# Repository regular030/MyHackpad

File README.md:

# BOM | SaturnBoard

- 16x 1N4148 Diodes
- 1x OLED 128x32 (Adafruit_SSD1306 would be good but not needed) 
- 16x Push Switches (SW_Push)
- 16x White keycaps
- 1x Seeed XIAO RP2040 MCU

THE REPO HAS BEEN CHANGED TO https://github.com/regular030/hackpad/tree/main

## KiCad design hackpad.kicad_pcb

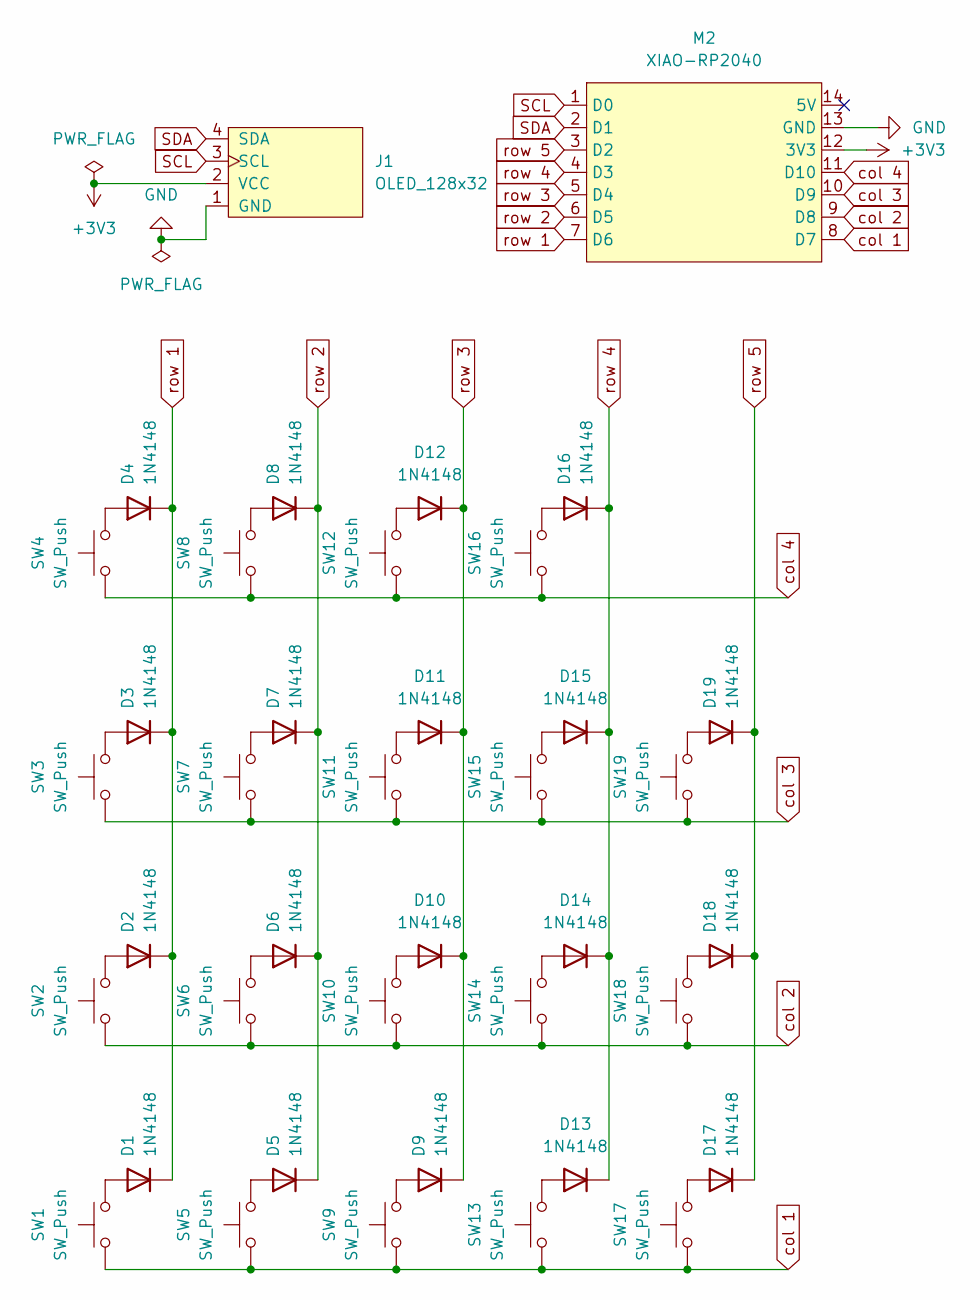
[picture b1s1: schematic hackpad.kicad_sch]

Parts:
D1, D2, D3, D4, D5, D6, D7, D8, D9, D10, D11, D12, D13, D14, D15, D16, D17, D18, D19: 1N4148; D_DO-35_SOD27_P7.62mm_Horizontal
J1: OLED_128x32; SSD1306-0.91-OLED-4pin-128x32
M2: XIAO-RP2040
SW1, SW2, SW3, SW4, SW5, SW6, SW7, SW8, SW9, SW10, SW11, SW12, SW13, SW14, SW15, SW16, SW17, SW18, SW19: SW_Push; SW_Cherry_MX_1.00u_PCB

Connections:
+3V3: J1.2 (VCC), M2.12 (3V3)
GND: J1.1 (GND), M2.13 (GND)
unnamed: D1.2 (A), SW1.2
unnamed: D2.2 (A), SW2.2
unnamed: D3.2 (A), SW3.2
unnamed: D4.2 (A), SW4.2
unnamed: D5.2 (A), SW5.2
unnamed: D6.2 (A), SW6.2
unnamed: D7.2 (A), SW7.2
unnamed: D8.2 (A), SW8.2
unnamed: D9.2 (A), SW9.2
unnamed: D10.2 (A), SW10.2
unnamed: D11.2 (A), SW11.2
unnamed: D12.2 (A), SW12.2
unnamed: D13.2 (A), SW13.2
unnamed: D14.2 (A), SW14.2
unnamed: D15.2 (A), SW15.2
unnamed: D16.2 (A), SW16.2
unnamed: D17.2 (A), SW17.2
unnamed: D18.2 (A), SW18.2
unnamed: D19.2 (A), SW19.2
SCL: J1.3 (SCL), M2.1 (D0)
SDA: J1.4 (SDA), M2.2 (D1)
col 1: M2.8 (D7), SW1.1, SW5.1, SW9.1, SW13.1, SW17.1
col 2: M2.9 (D8), SW2.1, SW6.1, SW10.1, SW14.1, SW18.1
col 3: M2.10 (D9), SW3.1, SW7.1, SW11.1, SW15.1, SW19.1
col 4: M2.11 (D10), SW4.1, SW8.1, SW12.1, SW16.1
row 1: D1.1 (K), D2.1 (K), D3.1 (K), D4.1 (K), M2.7 (D6)
row 2: D5.1 (K), D6.1 (K), D7.1 (K), D8.1 (K), M2.6 (D5)
row 3: D9.1 (K), D10.1 (K), D11.1 (K), D12.1 (K), M2.5 (D4)
row 4: D13.1 (K), D14.1 (K), D15.1 (K), D16.1 (K), M2.4 (D3)
row 5: D17.1 (K), D18.1 (K), D19.1 (K), M2.3 (D2)

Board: 2 copper layers, 40 parts (0 on the bottom side), 32 nets, no tracks yet.

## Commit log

2024-10-10 init
2024-10-10 changed some stuff
2024-10-17 Committed file changes, code is left
2024-10-17 added fireware. not done
2024-10-17 few changes
2024-10-17 change
